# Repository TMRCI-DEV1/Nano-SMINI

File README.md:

# Nano-SMINI
Arduino Nano-based CMRI SMINI

Shield: [![CC BY-SA 4.0][cc-by-sa-shield]][cc-by-sa]

This work is licensed under a
[Creative Commons Attribution-ShareAlike 4.0 International License][cc-by-sa].

[![CC BY-SA 4.0][cc-by-sa-image]][cc-by-sa]

[cc-by-sa]: http://creativecommons.org/licenses/by-sa/4.0/
[cc-by-sa-image]: https://licensebuttons.net/l/by-sa/4.0/88x31.png
[cc-by-sa-shield]: https://img.shields.io/badge/License-CC%20BY--SA%204.0-lightgrey.svg

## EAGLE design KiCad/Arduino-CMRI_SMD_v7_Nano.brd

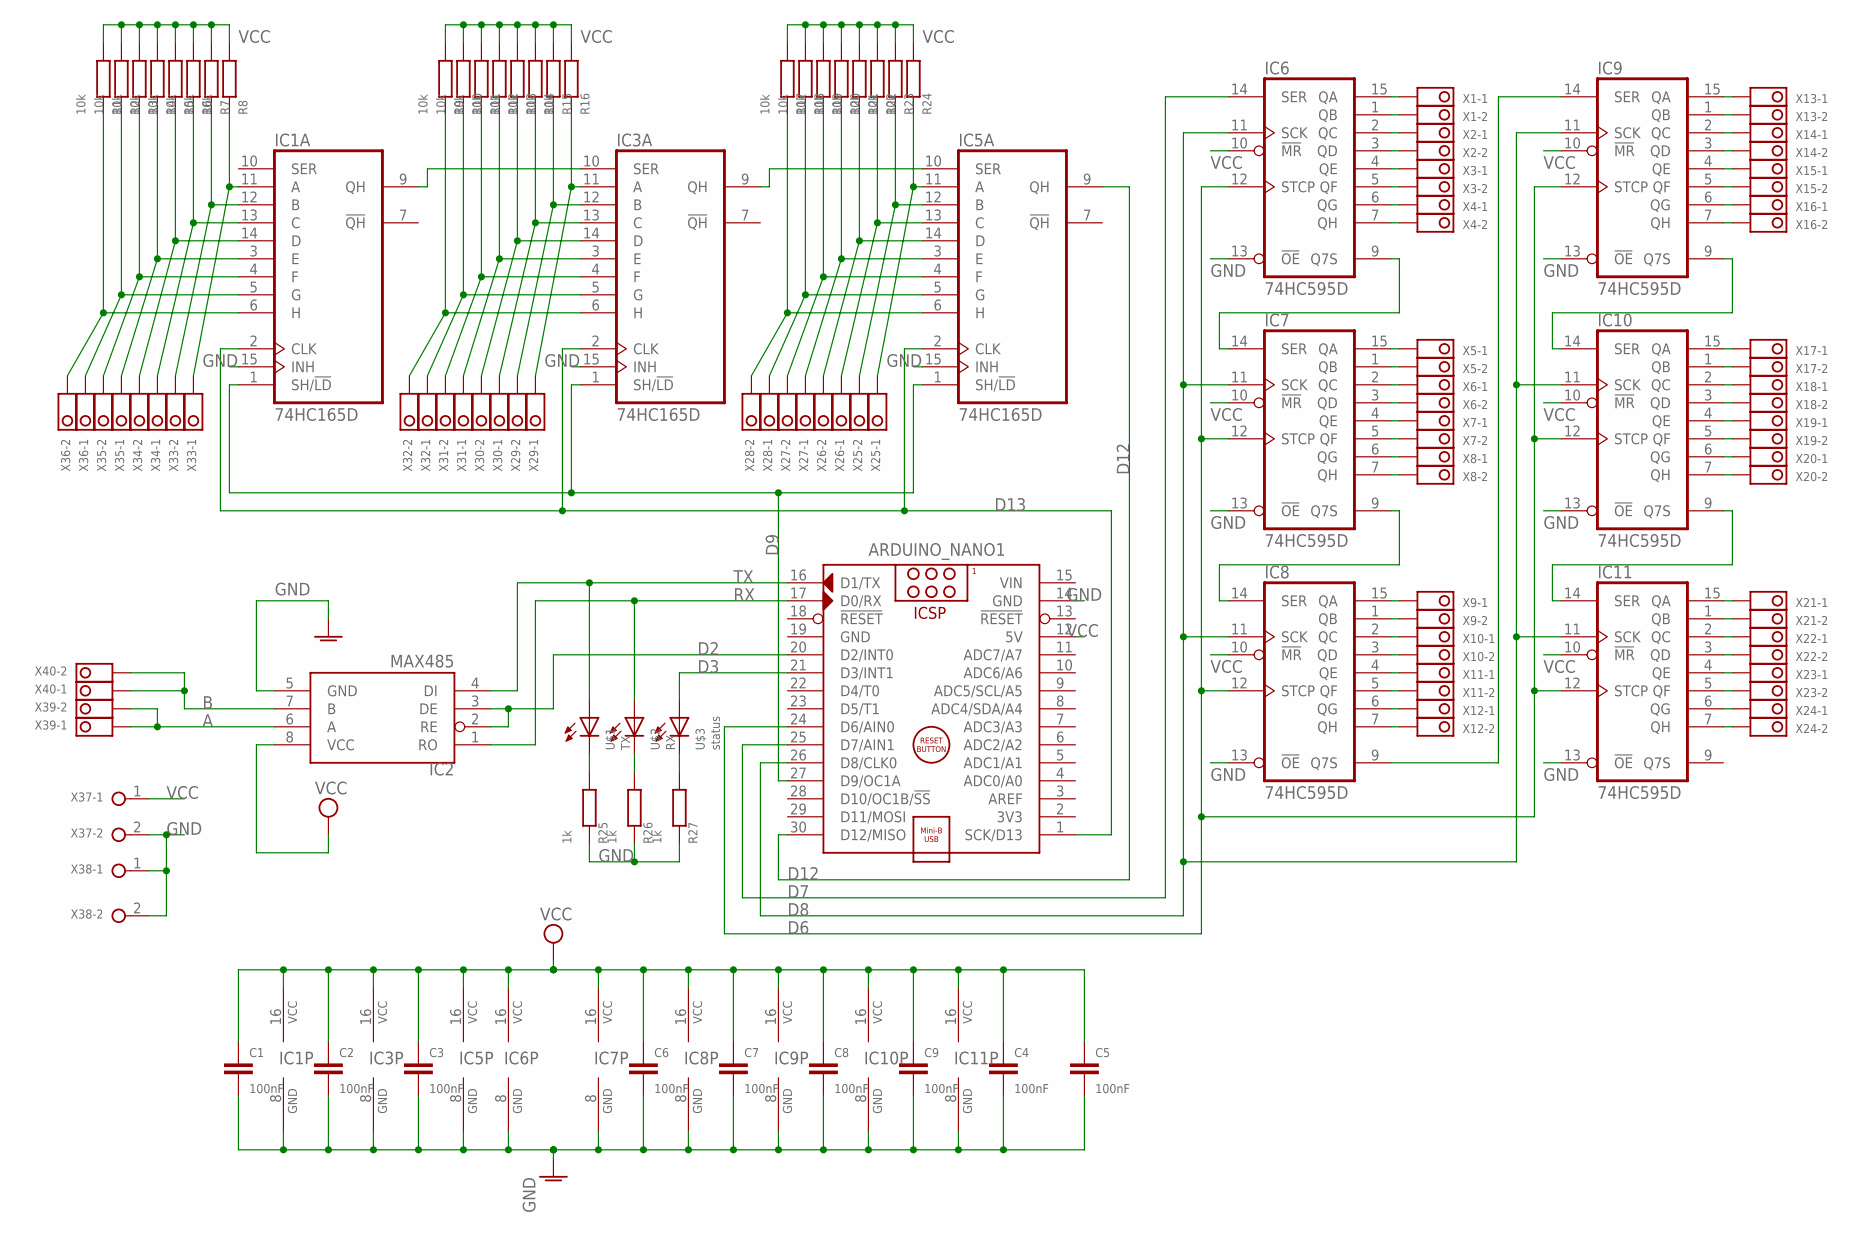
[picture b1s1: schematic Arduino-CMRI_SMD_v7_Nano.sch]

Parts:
ARDUINO_NANO1: ARDUINO_NANO
C1, C2, C3, C4, C5, C6, C7, C8, C9: 100nF; 1206
IC1, IC3, IC5: 74HC165D; SO16
IC2: MAX485; SO08
IC6, IC7, IC8, IC9, IC10, IC11: 74HC595D; SO16
R1, R2, R3, R4, R5, R6, R7, R8, R9, R10, R11, R12, R13, R14, R15, R16, R17, R18, R19, R20, R21, R22, R23, R24: 10k; R1206W
R25, R26, R27: 1k; R1206W
U$1: TX; CHIPLED_0603
U$2: RX; CHIPLED_0603
U$3: status; CHIPLED_0603
X1, X2, X3, X4, X5, X6, X7, X8, X9, X10, X11, X12, X13, X14, X15, X16, X17, X18, X19, X20, X21, X22, X23, X24, X25, X26, X27, X28, X29, X30, X31, X32, X33, X34, X35, X36, X39, X40: TERMINAL_2P_3,5MM_V2; TERMINAL_2P_3,5MM
X37, X38: TERMINAL-5MM-2POLE; W237-132

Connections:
A: IC2.6 (A), X39.P$1, X39.P$2
B: IC2.7 (B), X40.P$1, X40.P$2
D2: ARDUINO_NANO1.20 (D2/INT0), IC2.2 (RE), IC2.3 (DE)
D3: ARDUINO_NANO1.21 (D3/INT1), U$3.A
D6: ARDUINO_NANO1.24 (D6/AIN0), IC6.12 (STCP), IC7.12 (STCP), IC8.12 (STCP), IC9.12 (STCP), IC10.12 (STCP), IC11.12 (STCP)
D7: ARDUINO_NANO1.25 (D7/AIN1), IC6.14 (SER)
D8: ARDUINO_NANO1.26 (D8/CLK0), IC6.11 (SCK), IC7.11 (SCK), IC8.11 (SCK), IC9.11 (SCK), IC10.11 (SCK), IC11.11 (SCK)
D9: ARDUINO_NANO1.27 (D9/OC1A), IC1.1 (SH/!LD), IC3.1 (SH/!LD), IC5.1 (SH/!LD)
D12: ARDUINO_NANO1.30 (D12/MISO), IC5.9 (QH)
D13: ARDUINO_NANO1.1 (SCK/D13), IC1.2 (CLK), IC3.2 (CLK), IC5.2 (CLK)
GND: ARDUINO_NANO1.14 (GND), ARDUINO_NANO1.19 (GND), C1.1, C2.1, C3.1, C4.1, C5.1, C6.1, C7.1, C8.1, C9.1, IC1.8 (GND), IC1.15 (INH), IC2.5 (GND), IC3.8 (GND), IC3.15 (INH), IC5.8 (GND), IC5.15 (INH), IC6.8 (GND), IC6.13 (!OE), IC7.8 (GND), IC7.13 (!OE), IC8.8 (GND), IC8.13 (!OE), IC9.8 (GND), IC9.13 (!OE), IC10.8 (GND), IC10.13 (!OE), IC11.8 (GND), IC11.13 (!OE), R25.1, R26.1, R27.1, X37.2, X38.1, X38.2
unnamed: IC5.11 (A), R24.1, X25.P$1
unnamed: IC1.9 (QH), IC3.10 (SER)
unnamed: IC5.12 (B), R23.1, X25.P$2
unnamed: IC3.9 (QH), IC5.10 (SER)
unnamed: IC5.13 (C), R22.1, X26.P$1
unnamed: IC6.9 (Q7S), IC7.14 (SER)
unnamed: IC5.14 (D), R21.1, X26.P$2
unnamed: IC9.9 (Q7S), IC10.14 (SER)
unnamed: IC5.3 (E), R20.1, X27.P$1
unnamed: IC7.9 (Q7S), IC8.14 (SER)
unnamed: IC5.4 (F), R19.1, X27.P$2
unnamed: IC10.9 (Q7S), IC11.14 (SER)
unnamed: IC5.5 (G), R18.1, X28.P$1
unnamed: IC6.15 (QA), X1.P$1
unnamed: IC5.6 (H), R17.1, X28.P$2
unnamed: IC6.1 (QB), X1.P$2
unnamed: R25.2, U$1.C
unnamed: IC6.2 (QC), X2.P$1
unnamed: IC3.11 (A), R16.1, X29.P$1
unnamed: IC6.3 (QD), X2.P$2
unnamed: IC3.12 (B), R15.1, X29.P$2
unnamed: IC6.4 (QE), X3.P$1
unnamed: IC3.13 (C), R14.1, X30.P$1
unnamed: IC6.5 (QF), X3.P$2
unnamed: IC3.14 (D), R13.1, X30.P$2
unnamed: IC6.6 (QG), X4.P$1
unnamed: IC3.3 (E), R12.1, X31.P$1
unnamed: IC6.7 (QH), X4.P$2
unnamed: IC3.4 (F), R11.1, X31.P$2
unnamed: IC7.15 (QA), X5.P$1
unnamed: IC3.5 (G), R10.1, X32.P$1
unnamed: IC7.1 (QB), X5.P$2
unnamed: IC3.6 (H), R9.1, X32.P$2
unnamed: IC7.2 (QC), X6.P$1
unnamed: IC1.11 (A), R8.1, X33.P$1
unnamed: IC7.3 (QD), X6.P$2
unnamed: IC1.12 (B), R7.1, X33.P$2
unnamed: IC7.4 (QE), X7.P$1
unnamed: IC1.13 (C), R6.1, X34.P$1
unnamed: IC7.5 (QF), X7.P$2
unnamed: IC1.14 (D), R5.1, X34.P$2
unnamed: IC7.6 (QG), X8.P$1
unnamed: IC1.3 (E), R4.1, X35.P$1
unnamed: IC7.7 (QH), X8.P$2
unnamed: IC1.4 (F), R3.1, X35.P$2
unnamed: IC8.15 (QA), X9.P$1
unnamed: IC1.5 (G), R2.1, X36.P$1
unnamed: IC8.1 (QB), X9.P$2
unnamed: IC8.2 (QC), X10.P$1
unnamed: IC8.3 (QD), X10.P$2
unnamed: IC8.9 (Q7S), IC9.14 (SER)
unnamed: IC8.4 (QE), X11.P$1
unnamed: IC8.5 (QF), X11.P$2
unnamed: R26.2, U$2.C
unnamed: IC1.6 (H), R1.1, X36.P$2
unnamed: R27.2, U$3.C
unnamed: IC8.6 (QG), X12.P$1
unnamed: IC8.7 (QH), X12.P$2
unnamed: IC9.15 (QA), X13.P$1
unnamed: IC9.1 (QB), X13.P$2
unnamed: IC9.2 (QC), X14.P$1
unnamed: IC9.3 (QD), X14.P$2
unnamed: IC9.4 (QE), X15.P$1
unnamed: IC9.5 (QF), X15.P$2
unnamed: IC9.6 (QG), X16.P$1
unnamed: IC9.7 (QH), X16.P$2
unnamed: IC10.15 (QA), X17.P$1
unnamed: IC10.1 (QB), X17.P$2
unnamed: IC10.2 (QC), X18.P$1
unnamed: IC10.3 (QD), X18.P$2
unnamed: IC10.4 (QE), X19.P$1
unnamed: IC10.5 (QF), X19.P$2
unnamed: IC10.6 (QG), X20.P$1
unnamed: IC10.7 (QH), X20.P$2
unnamed: IC11.15 (QA), X21.P$1
unnamed: IC11.1 (QB), X21.P$2
unnamed: IC11.2 (QC), X22.P$1
unnamed: IC11.3 (QD), X22.P$2
unnamed: IC11.4 (QE), X23.P$1
unnamed: IC11.5 (QF), X23.P$2
unnamed: IC11.6 (QG), X24.P$1
unnamed: IC11.7 (QH), X24.P$2
RX: ARDUINO_NANO1.17 (D0/RX), IC2.1 (RO), U$2.A
TX: ARDUINO_NANO1.16 (D1/TX), IC2.4 (DI), U$1.A
VCC: ARDUINO_NANO1.12 (5V), C1.2, C2.2, C3.2, C4.2, C5.2, C6.2, C7.2, C8.2, C9.2, IC1.16 (VCC), IC2.8 (VCC), IC3.16 (VCC), IC5.16 (VCC), IC6.10 (!MR), IC6.16 (VCC), IC7.10 (!MR), IC7.16 (VCC), IC8.10 (!MR), IC8.16 (VCC), IC9.10 (!MR), IC9.16 (VCC), IC10.10 (!MR), IC10.16 (VCC), IC11.10 (!MR), IC11.16 (VCC), R1.2, R2.2, R3.2, R4.2, R5.2, R6.2, R7.2, R8.2, R9.2, R10.2, R11.2, R12.2, R13.2, R14.2, R15.2, R16.2, R17.2, R18.2, R19.2, R20.2, R21.2, R22.2, R23.2, R24.2, X37.1
VIN: ARDUINO_NANO1.15 (VIN)

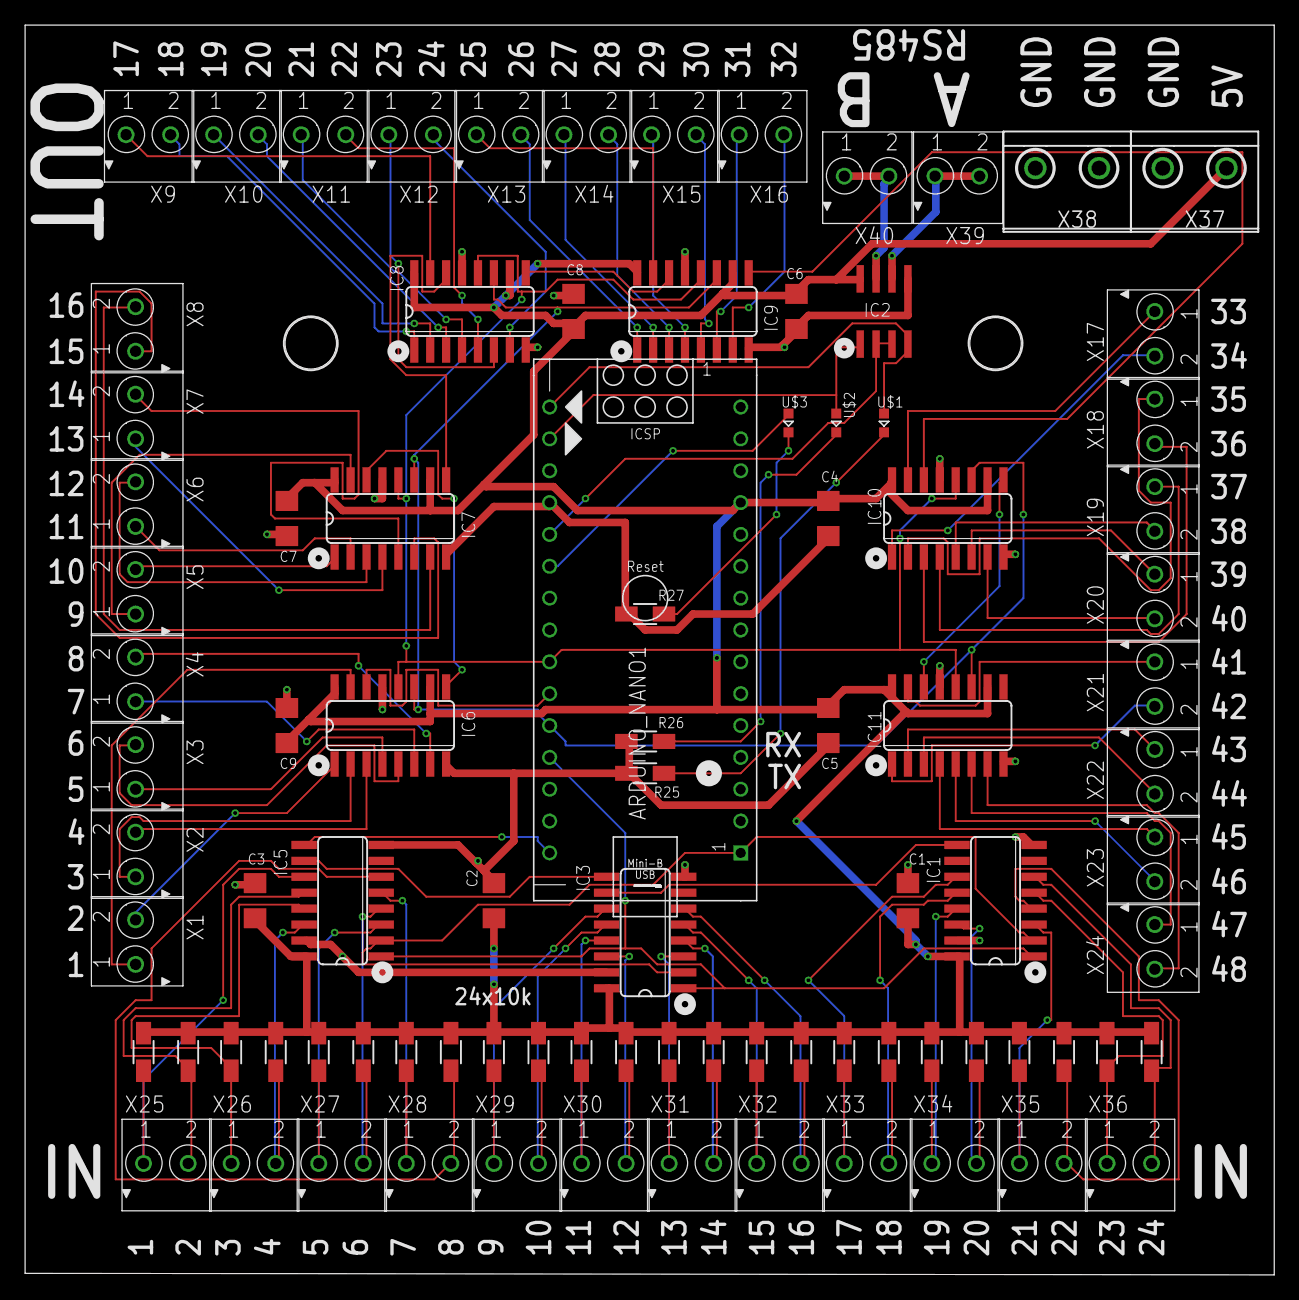
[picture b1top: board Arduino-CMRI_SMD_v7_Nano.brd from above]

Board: 2 copper layers, 99.6 x 99.7 mm, 92 parts (0 on the bottom side), 96 nets.

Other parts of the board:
H1, H2: MOUNT-HOLE4.1; 4,1

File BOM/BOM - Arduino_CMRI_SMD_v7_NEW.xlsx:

Designators | Value | Footprint | Manufacturer Part Number | Quantity
C1, C2, C3, C4, C5, C6, C7, C8, C9 | 100nF | 1206 | CL31B104KBCNNNC | 9
R1, R2, R3, R4, R5, R6, R7, R8, R9, R10, R11, R12, R13, R14, R15, R16, R17, R18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 | 10k | 1206 | 1206W4F1002T5E | 24
R25, R26, R27 | 1k | 1206 | 1206W4F1001T5 | 3
X1, X2, X3, X4, X5, X6, X7, X8, X9, X10, X11, X12, X13, X14, X15, X16, X17, X18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 | TERMINAL_7.5X7.3MM_TM | TERMINAL_7.5X7.3MM_TM | KF350-3.5-2P | 38
X37, X38 | TERMINAL_10.16X8.1MM_TM | TERMINAL_10.16X8.1MM_TM | WJ128V-5.0-2P | 2
IC6, IC7, IC8, IC9, IC10, IC11 | 74HC595D | SOP16_150MIL | 74HC595D | 6
IC1, IC3, IC5 | 74HC165D, 653 | SOIC16_150MIL | 74HC165D,653 | 3
H1, H2 | MOUNT-HOLE4.1 | 4,1 |  | 2 |  | DNP
ARDUINO_NANO1 |  | ARDUINO_NANO_HEADERS | 15Fx1-254mm | 2 |  | DNP | 15Fx1-254mm
IC2 | MAX485 | SOP8 | MAX485ED | 1
U$1 | TX，CHIPLED_0603, blue | 0603 | LTST-C190TBKT | 1
U$2 | RX，CHIPLED_0603, red | 0603 | LTST-C190KRKT | 1
U$3 | status，CHIPLED_0603, yellow | 0603 | LTST-C190KSKT | 1

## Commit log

2023-04-12 Added full project
2023-05-17 Update Current_OPT_SMINI_Node.ino
    Latest version
2023-05-17 Update Current_OPT_SMINI_Node.ino
    Added header
2023-05-23 Update LICENSE
